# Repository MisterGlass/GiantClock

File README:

This is a pet project of mine.

Right now, most of the files here are incomplete, stubs, or placeholders.

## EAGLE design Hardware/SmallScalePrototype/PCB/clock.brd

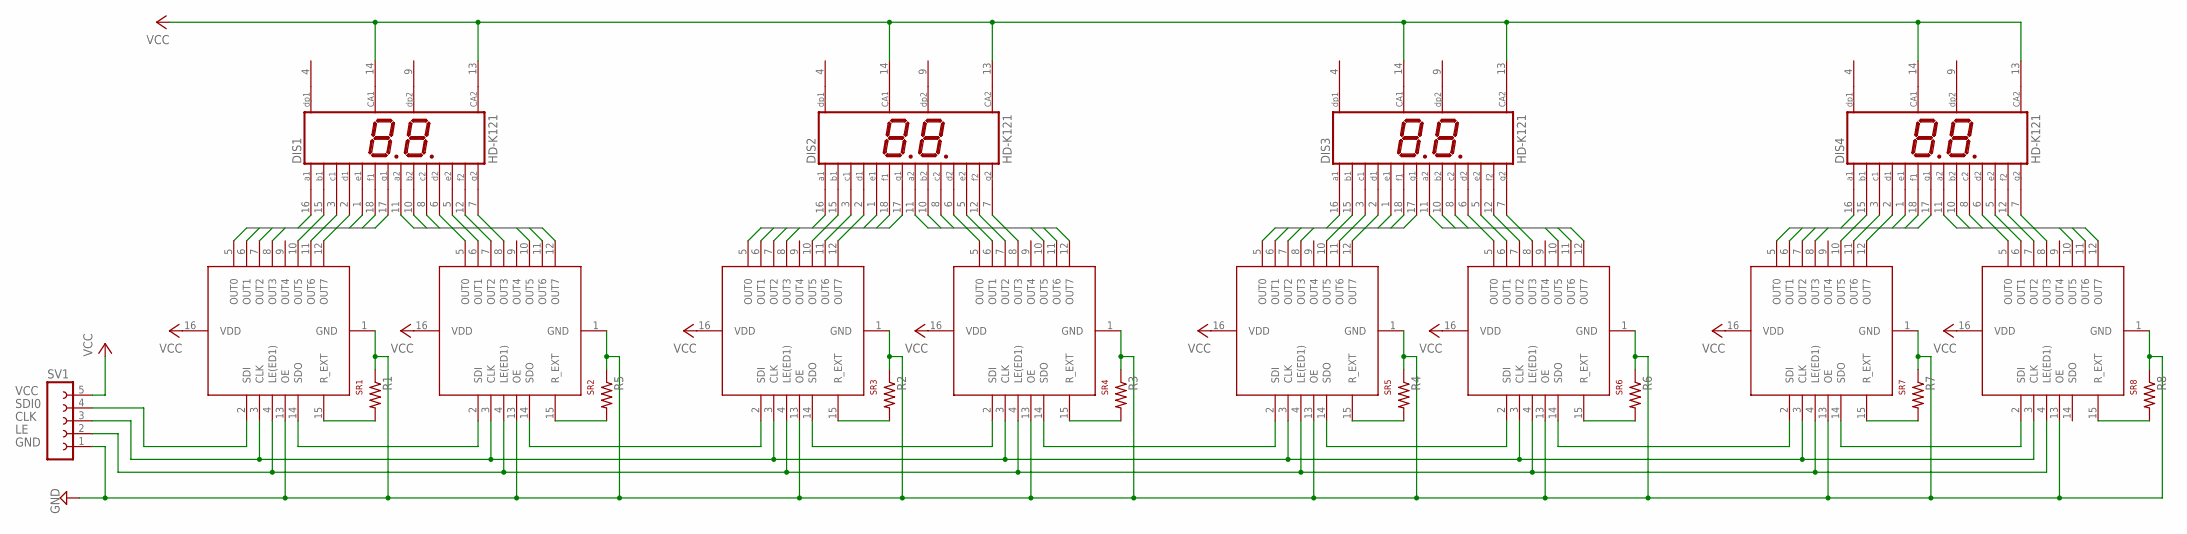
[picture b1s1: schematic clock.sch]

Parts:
DIS1, DIS2, DIS3, DIS4: HD-K121; HDSP-R
R1, R2, R3, R4, R5, R6, R7, R8: R-US_R0603; R0603
SR1, SR2, SR3, SR4, SR5, SR6, SR7, SR8: TLC5916/17; SOIC-16
SV1: FE05-1

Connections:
CLK: SR1.3 (CLK), SR2.3 (CLK), SR3.3 (CLK), SR4.3 (CLK), SR5.3 (CLK), SR6.3 (CLK), SR7.3 (CLK), SR8.3 (CLK), SV1.3
DAYSONES0: DIS1.11 (A2), SR2.11 (OUT6)
DAYSONES1: DIS1.10 (B2), SR2.12 (OUT7)
DAYSONES2: DIS1.8 (C2), SR2.5 (OUT0)
DAYSONES3: DIS1.6 (D2), SR2.7 (OUT2)
DAYSONES4: DIS1.5 (E2), SR2.8 (OUT3)
DAYSONES5: DIS1.12 (F2), SR2.10 (OUT5)
DAYSONES6: DIS1.7 (G2), SR2.6 (OUT1)
DAYSTENS0: DIS1.16 (A1), SR1.7 (OUT2)
DAYSTENS1: DIS1.15 (B1), SR1.8 (OUT3)
DAYSTENS2: DIS1.3 (C1), SR1.10 (OUT5)
DAYSTENS3: DIS1.2 (D1), SR1.11 (OUT6)
DAYSTENS4: DIS1.1 (E1), SR1.12 (OUT7)
DAYSTENS5: DIS1.18 (F1), SR1.5 (OUT0)
DAYSTENS6: DIS1.17 (G1), SR1.6 (OUT1)
GND: R1.1, R2.1, R3.1, R4.1, R5.1, R6.1, R7.1, R8.1, SR1.1 (GND), SR1.13 (OE), SR2.1 (GND), SR2.13 (OE), SR3.1 (GND), SR3.13 (OE), SR4.1 (GND), SR4.13 (OE), SR5.1 (GND), SR5.13 (OE), SR6.1 (GND), SR6.13 (OE), SR7.1 (GND), SR7.13 (OE), SR8.1 (GND), SR8.13 (OE), SV1.1
HOURSONES0: DIS2.11 (A2), SR4.11 (OUT6)
HOURSONES1: DIS2.10 (B2), SR4.12 (OUT7)
HOURSONES2: DIS2.8 (C2), SR4.5 (OUT0)
HOURSONES3: DIS2.6 (D2), SR4.7 (OUT2)
HOURSONES4: DIS2.5 (E2), SR4.8 (OUT3)
HOURSONES5: DIS2.12 (F2), SR4.10 (OUT5)
HOURSONES6: DIS2.7 (G2), SR4.6 (OUT1)
HOURSTENS0: DIS2.16 (A1), SR3.7 (OUT2)
HOURSTENS1: DIS2.15 (B1), SR3.8 (OUT3)
HOURSTENS2: DIS2.3 (C1), SR3.10 (OUT5)
HOURSTENS3: DIS2.2 (D1), SR3.11 (OUT6)
HOURSTENS4: DIS2.1 (E1), SR3.12 (OUT7)
HOURSTENS5: DIS2.18 (F1), SR3.5 (OUT0)
HOURSTENS6: DIS2.17 (G1), SR3.6 (OUT1)
LE: SR1.4 (LE(ED1)), SR2.4 (LE(ED1)), SR3.4 (LE(ED1)), SR4.4 (LE(ED1)), SR5.4 (LE(ED1)), SR6.4 (LE(ED1)), SR7.4 (LE(ED1)), SR8.4 (LE(ED1)), SV1.2
MINUTESONES0: DIS3.11 (A2), SR6.11 (OUT6)
MINUTESONES1: DIS3.10 (B2), SR6.12 (OUT7)
MINUTESONES2: DIS3.8 (C2), SR6.5 (OUT0)
MINUTESONES3: DIS3.6 (D2), SR6.7 (OUT2)
MINUTESONES4: DIS3.5 (E2), SR6.8 (OUT3)
MINUTESONES5: DIS3.12 (F2), SR6.10 (OUT5)
MINUTESONES6: DIS3.7 (G2), SR6.6 (OUT1)
MINUTESTENS0: DIS3.16 (A1), SR5.7 (OUT2)
MINUTESTENS1: DIS3.15 (B1), SR5.8 (OUT3)
MINUTESTENS2: DIS3.3 (C1), SR5.10 (OUT5)
MINUTESTENS3: DIS3.2 (D1), SR5.11 (OUT6)
MINUTESTENS4: DIS3.1 (E1), SR5.12 (OUT7)
MINUTESTENS5: DIS3.18 (F1), SR5.5 (OUT0)
MINUTESTENS6: DIS3.17 (G1), SR5.6 (OUT1)
unnamed: R3.2, SR4.15 (R_EXT)
unnamed: R2.2, SR3.15 (R_EXT)
unnamed: R5.2, SR2.15 (R_EXT)
unnamed: R1.2, SR1.15 (R_EXT)
unnamed: R6.2, SR6.15 (R_EXT)
unnamed: R4.2, SR5.15 (R_EXT)
unnamed: R8.2, SR8.15 (R_EXT)
unnamed: R7.2, SR7.15 (R_EXT)
SDI0: SR1.2 (SDI), SV1.4
SDI1: SR1.14 (SDO), SR2.2 (SDI)
SDI2: SR2.14 (SDO), SR3.2 (SDI)
SDI3: SR3.14 (SDO), SR4.2 (SDI)
SDI4: SR4.14 (SDO), SR5.2 (SDI)
SDI5: SR5.14 (SDO), SR6.2 (SDI)
SDI6: SR6.14 (SDO), SR7.2 (SDI)
SDI7: SR7.14 (SDO), SR8.2 (SDI)
SECONDSONES0: DIS4.11 (A2), SR8.11 (OUT6)
SECONDSONES1: DIS4.10 (B2), SR8.12 (OUT7)
SECONDSONES2: DIS4.8 (C2), SR8.5 (OUT0)
SECONDSONES3: DIS4.6 (D2), SR8.7 (OUT2)
SECONDSONES4: DIS4.5 (E2), SR8.8 (OUT3)
SECONDSONES5: DIS4.12 (F2), SR8.10 (OUT5)
SECONDSONES6: DIS4.7 (G2), SR8.6 (OUT1)
SECONDSTENS0: DIS4.16 (A1), SR7.7 (OUT2)
SECONDSTENS1: DIS4.15 (B1), SR7.8 (OUT3)
SECONDSTENS2: DIS4.3 (C1), SR7.10 (OUT5)
SECONDSTENS3: DIS4.2 (D1), SR7.11 (OUT6)
SECONDSTENS4: DIS4.1 (E1), SR7.12 (OUT7)
SECONDSTENS5: DIS4.18 (F1), SR7.5 (OUT0)
SECONDSTENS6: DIS4.17 (G1), SR7.6 (OUT1)
VCC: DIS1.13 (CA2), DIS1.14 (CA1), DIS2.13 (CA2), DIS2.14 (CA1), DIS3.13 (CA2), DIS3.14 (CA1), DIS4.13 (CA2), DIS4.14 (CA1), SR1.16 (VDD), SR2.16 (VDD), SR3.16 (VDD), SR4.16 (VDD), SR5.16 (VDD), SR6.16 (VDD), SR7.16 (VDD), SR8.16 (VDD), SV1.5

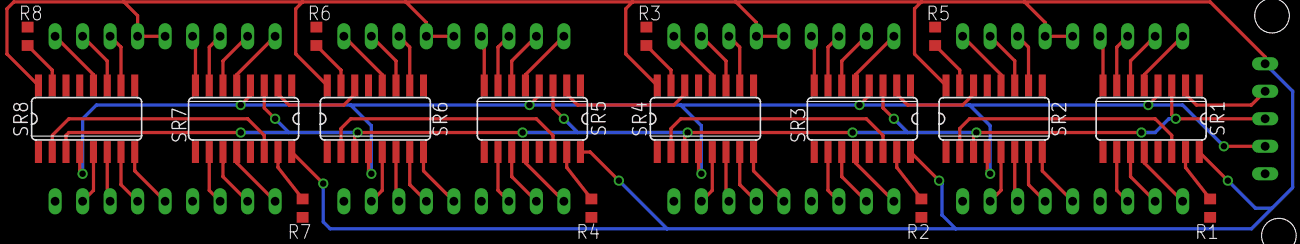
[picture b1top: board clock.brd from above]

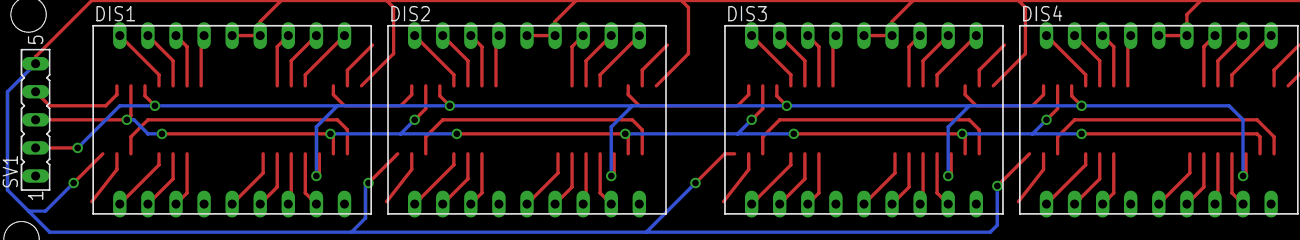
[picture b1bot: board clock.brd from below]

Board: 2 copper layers, 21 parts (5 on the bottom side), 76 nets.

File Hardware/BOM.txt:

4x HD-K121 (2 digit 7seg display)
8x TLC5916/17 (shift register)

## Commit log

2013-08-20 First!
    Mostly placeholders
2013-08-20 Organizing
2013-08-25 Small board work
2013-08-26 Schematic v1
    I think thats everything....
2013-08-26 Fixed ERC warning
2013-08-28 Most of the board work
2013-08-30 minor brd work
2013-08-30 All wires routed, passing OSHPark DRC!
2013-08-30 Centered displays, added mounting holes
2013-08-30 minor brd tweaks
2013-09-10 reference images
    reference shot from the first episode and a mockup based on extrapolated
    measurements.
2013-11-21 Initial software wok (very broken)
2013-11-22 More software work. CLock logic now works, but failing to drive teh LED displays
